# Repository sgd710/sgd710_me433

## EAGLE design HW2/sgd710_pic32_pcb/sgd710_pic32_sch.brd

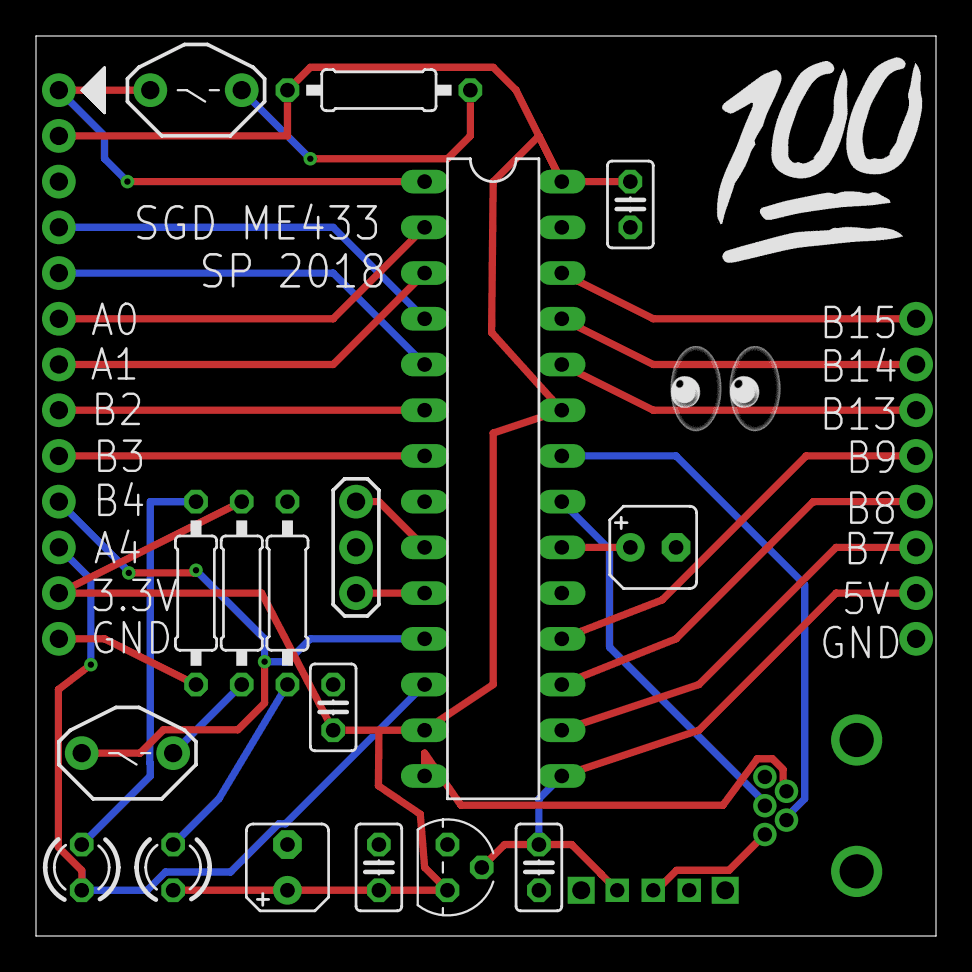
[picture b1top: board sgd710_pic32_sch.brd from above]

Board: 2 copper layers, 50.0 x 50.0 mm, 22 parts (1 on the bottom side), 29 nets.

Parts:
C1, C2, C3, C4: 0.1uF; C025-025X050
C5, C6: 10uF; B45181A
J1: USB-MB-H
LED1: GREEN; LED3MM
LED2: RED; LED3MM
R1, R2: 330; 0207/10
R3, R4: 10k; 0207/10
U$1: PIC23MX250F128B; DIL28-3
U$2: SLIDES; SLIDE
U$3: MCP1702; TO92
U$4: RESET; PB
U$5: USER; PB
U$6, U$7: CONN_8; 1X08
U$8: PICKIT; 1X05
U$9: 8MHz; OSC

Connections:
+3V3: C1.1, C2.1, C4.1, C6.+, LED2.A, R3.1, R4.1, U$1.13, U$1.23, U$1.28, U$3.3, U$7.2, U$8.2
+5V: C3.1, U$1.15, U$2.1, U$3.2, U$6.2
A0: U$1.2, U$7.8
A1: U$1.3, U$7.7
A4/LED: LED1.A, U$1.12, U$7.3
B2: U$1.6, U$7.6
B3: U$1.7, U$7.5
B4/USER: U$1.11, U$5.2, U$7.4
B7: U$1.16, U$6.3
B8: U$1.17, U$6.4
B9: U$1.18, U$6.5
B13: U$1.24, U$6.6
B14: U$1.25, U$6.7
B15: U$1.26, U$6.8
D+: J1.D+, U$1.21
D-: J1.D-, U$1.22
GND: C1.2, C2.2, C3.2, C4.2, C5.-, C6.-, J1.GND, R1.1, R2.1, U$1.8, U$1.19, U$1.27, U$6.1, U$7.1, U$8.3, U$9.2
MCLR: U$1.1, U$4.2, U$8.1
unnamed: J1.VBUS, U$2.2
unnamed: LED2.K, R1.2
unnamed: U$1.9, U$9.3
unnamed: U$1.10, U$9.1
unnamed: LED1.K, R2.2
unnamed: C5.+, U$1.20
unnamed: R3.2, U$4.1
unnamed: R4.2, U$5.1
PGC: U$1.5, U$8.5
PGD: U$1.4, U$8.4
USBID: J1.ID, U$1.14

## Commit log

2018-04-08 3.3V
2018-04-08 Revert "3.3V"
    This reverts commit e0ab8e79c60285a142d939258e12a75b32b024e6.
2018-04-16 4/16/18
2018-04-17 4/17/18
2018-04-23 4/23/18
2018-05-16 5/15/18
2018-06-14 6/14/18
2018-06-15 6/15/18
2018-06-16 6/16/18
